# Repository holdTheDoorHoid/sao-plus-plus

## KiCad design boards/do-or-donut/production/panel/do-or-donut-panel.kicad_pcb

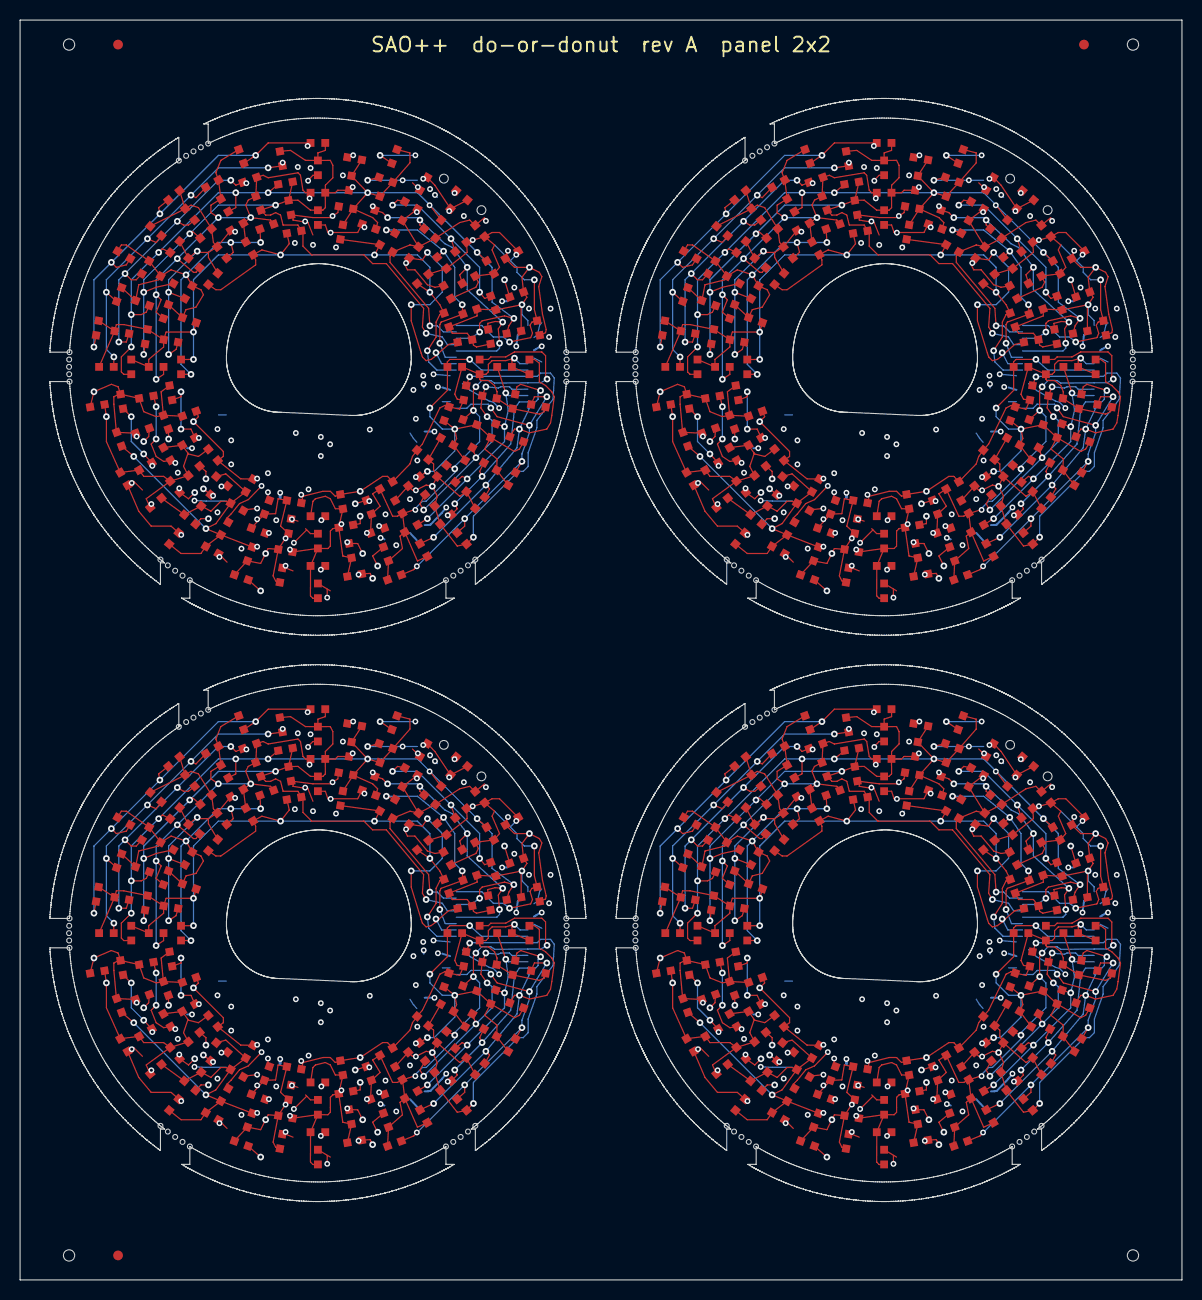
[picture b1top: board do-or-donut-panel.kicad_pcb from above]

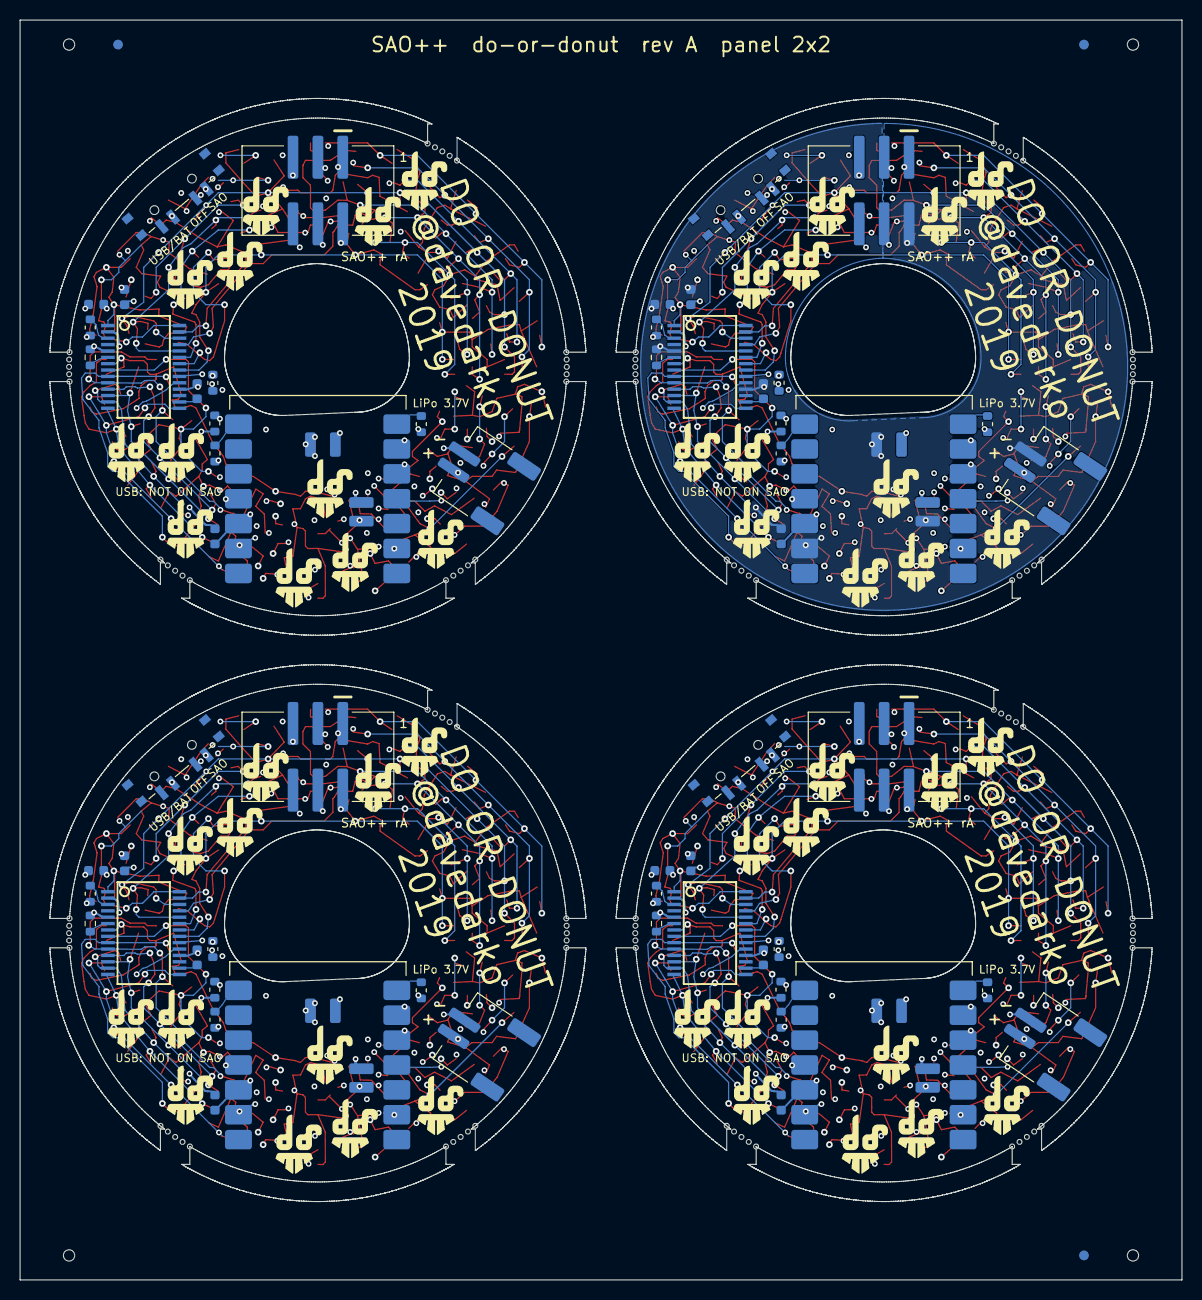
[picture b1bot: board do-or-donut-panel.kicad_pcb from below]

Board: 4 copper layers, 118.6 x 128.6 mm, 636 parts (60 on the bottom side), 136 nets.

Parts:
C101, C103, C104, C105, C201, C203, C204, C205, C301, C303, C304, C305, C401, C403, C404, C405: 100n; SAOPP_C_0603_1608Metric
DA101, DA102, DA103, DA104, DA105, DA106, DA107, DA108, DA109, DA110, DA111, DA112, DA113, DA114, DA115, DA116, DA117, DA118, DA119, DA120, DA121, DA122, DA123, DA124, DA125, DA126, DA127, DA128, DA129, DA130, DA131, DA132, DA133, DA134, DA135, DA136, DA137, DA138, DA139, DA140, DA141, DA142, DA143, DA144, DA145, DA146, DA147, DA148, DA149, DA150, DA151, DA152, DA153, DA154, DA155, DA156, DA157, DA158, DA159, DA160, DA161, DA162, DA163, DA164, DA165, DA166, DA167, DA168, DA169, DA170, DA171, DA172, DA201, DA202, DA203, DA204, DA205, DA206, DA207, DA208, DA209, DA210, DA211, DA212, DA213, DA214, DA215, DA216, DA217, DA218, DA219, DA220, DA221, DA222, DA223, DA224, DA225, DA226, DA227, DA228, DA229, DA230, DA231, DA232, DA233, DA234, DA235, DA236, DA237, DA238, DA239, DA240, DA241, DA242, DA243, DA244, DA245, DA246, DA247, DA248, DA249, DA250, DA251, DA252, DA253, DA254, DA255, DA256, DA257, DA258, DA259, DA260, DA261, DA262, DA263, DA264, DA265, DA266, DA267, DA268, DA269, DA270, DA271, DA272, DA301, DA302, DA303, DA304, DA305, DA306, DA307, DA308, DA309, DA310, DA311, DA312, DA313, DA314, DA315, DA316, DA317, DA318, DA319, DA320, DA321, DA322, DA323, DA324, DA325, DA326, DA327, DA328, DA329, DA330, DA331, DA332, DA333, DA334, DA335, DA336, DA337, DA338, DA339, DA340, DA341, DA342, DA343, DA344, DA345, DA346, DA347, DA348, DA349, DA350, DA351, DA352, DA353, DA354, DA355, DA356, DA357, DA358, DA359, DA360, DA361, DA362, DA363, DA364, DA365, DA366, DA367, DA368, DA369, DA370, DA371, DA372, DA401, DA402, DA403, DA404, DA405, DA406, DA407, DA408, DA409, DA410, DA411, DA412, DA413, DA414, DA415, DA416, DA417, DA418, DA419, DA420, DA421, DA422, DA423, DA424, DA425, DA426, DA427, DA428, DA429, DA430, DA431, DA432, DA433, DA434, DA435, DA436, DA437, DA438, DA439, DA440, DA441, DA442, DA443, DA444, DA445, DA446, DA447, DA448, DA449, DA450, DA451, DA452, DA453, DA454, DA455, DA456, DA457, DA458, DA459, DA460, DA461, DA462, DA463, DA464, DA465, DA466, DA467, DA468, DA469, DA470, DA471, DA472: LED 0603; LED_0603_CHIP-LED0603_davedarko
DB101, DB102, DB103, DB104, DB105, DB106, DB107, DB108, DB109, DB110, DB111, DB112, DB113, DB114, DB115, DB116, DB117, DB118, DB119, DB120, DB121, DB122, DB123, DB124, DB125, DB126, DB127, DB128, DB129, DB130, DB131, DB132, DB133, DB134, DB135, DB136, DB137, DB138, DB139, DB140, DB141, DB142, DB143, DB144, DB145, DB146, DB147, DB148, DB149, DB150, DB151, DB152, DB153, DB154, DB155, DB156, DB157, DB158, DB159, DB160, DB161, DB162, DB163, DB164, DB165, DB166, DB167, DB168, DB169, DB170, DB171, DB172, DB201, DB202, DB203, DB204, DB205, DB206, DB207, DB208, DB209, DB210, DB211, DB212, DB213, DB214, DB215, DB216, DB217, DB218, DB219, DB220, DB221, DB222, DB223, DB224, DB225, DB226, DB227, DB228, DB229, DB230, DB231, DB232, DB233, DB234, DB235, DB236, DB237, DB238, DB239, DB240, DB241, DB242, DB243, DB244, DB245, DB246, DB247, DB248, DB249, DB250, DB251, DB252, DB253, DB254, DB255, DB256, DB257, DB258, DB259, DB260, DB261, DB262, DB263, DB264, DB265, DB266, DB267, DB268, DB269, DB270, DB271, DB272, DB301, DB302, DB303, DB304, DB305, DB306, DB307, DB308, DB309, DB310, DB311, DB312, DB313, DB314, DB315, DB316, DB317, DB318, DB319, DB320, DB321, DB322, DB323, DB324, DB325, DB326, DB327, DB328, DB329, DB330, DB331, DB332, DB333, DB334, DB335, DB336, DB337, DB338, DB339, DB340, DB341, DB342, DB343, DB344, DB345, DB346, DB347, DB348, DB349, DB350, DB351, DB352, DB353, DB354, DB355, DB356, DB357, DB358, DB359, DB360, DB361, DB362, DB363, DB364, DB365, DB366, DB367, DB368, DB369, DB370, DB371, DB372, DB401, DB402, DB403, DB404, DB405, DB406, DB407, DB408, DB409, DB410, DB411, DB412, DB413, DB414, DB415, DB416, DB417, DB418, DB419, DB420, DB421, DB422, DB423, DB424, DB425, DB426, DB427, DB428, DB429, DB430, DB431, DB432, DB433, DB434, DB435, DB436, DB437, DB438, DB439, DB440, DB441, DB442, DB443, DB444, DB445, DB446, DB447, DB448, DB449, DB450, DB451, DB452, DB453, DB454, DB455, DB456, DB457, DB458, DB459, DB460, DB461, DB462, DB463, DB464, DB465, DB466, DB467, DB468, DB469, DB470, DB471, DB472: LED 0603; LED_0603_CHIP-LED0603_davedarko
J101, J201, J301, J401: SAO v1.69bis; SAOPP_CONN-01_BoxHeader_2x03_P2.54mm_SMD_XFCN_BH254VS-6P
J102, J202, J302, J402: LiPo 3.7 V; SAOPP_CONN-10_JST_PH_S2B-PH-SM4-TB_1x02_Horizontal
R101, R104, R105, R201, R204, R205, R301, R304, R305, R401, R404, R405: 1.3k; SAOPP_R_0603_1608Metric
R106, R206, R306, R406: 20k; R_0603_1608Metric
R107, R108, R207, R208, R307, R308, R407, R408: 330; SAOPP_R_0603_1608Metric
SW101, SW201, SW301, SW401: SAO / OFF / USB-BAT; SAOPP_SW-01_Slide_SP3T_CK_PCM13SMTR
U101, U201, U301, U401: IS31FL3731; SSOP-28_IS31FL3731_davedarko
U102, U202, U302, U402: XIAO ESP32-C3 / S3 / C6; SAOPP_MCU-01_Seeed_XIAO_SMD_C3_S3_C6

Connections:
B2-BAT+: J202.1, U202.15
B2-CA1: DA201.1, DA202.1, DA203.1, DA204.1, DA205.1, DA206.1, DA207.1, DA208.1, DA216.2, DA224.2, DA232.2, DA240.2, DA248.2, DA256.2, DA264.2, DA272.2, U201.21
B2-CA2: DA208.2, DA209.1, DA210.1, DA211.1, DA212.1, DA213.1, DA214.1, DA215.1, DA216.1, DA223.2, DA231.2, DA239.2, DA247.2, DA255.2, DA263.2, DA271.2, U201.22
B2-CA3: DA207.2, DA215.2, DA217.1, DA218.1, DA219.1, DA220.1, DA221.1, DA222.1, DA223.1, DA224.1, DA230.2, DA238.2, DA246.2, DA254.2, DA262.2, DA270.2, U201.23
B2-CA4: DA206.2, DA214.2, DA222.2, DA225.1, DA226.1, DA227.1, DA228.1, DA229.1, DA230.1, DA231.1, DA232.1, DA237.2, DA245.2, DA253.2, DA261.2, DA269.2, U201.24
B2-CA5: DA205.2, DA213.2, DA221.2, DA229.2, DA233.1, DA234.1, DA235.1, DA236.1, DA237.1, DA238.1, DA239.1, DA240.1, DA244.2, DA252.2, DA260.2, DA268.2, U201.25
B2-CA6: DA204.2, DA212.2, DA220.2, DA228.2, DA236.2, DA241.1, DA242.1, DA243.1, DA244.1, DA245.1, DA246.1, DA247.1, DA248.1, DA251.2, DA259.2, DA267.2, U201.26
B2-CA7: DA203.2, DA211.2, DA219.2, DA227.2, DA235.2, DA243.2, DA249.1, DA250.1, DA251.1, DA252.1, DA253.1, DA254.1, DA255.1, DA256.1, DA258.2, DA266.2, U201.27
B2-CA8: DA202.2, DA210.2, DA218.2, DA226.2, DA234.2, DA242.2, DA250.2, DA257.1, DA258.1, DA259.1, DA260.1, DA261.1, DA262.1, DA263.1, DA264.1, DA265.2, U201.28
B2-CA9: DA201.2, DA209.2, DA217.2, DA225.2, DA233.2, DA241.2, DA249.2, DA257.2, DA265.1, DA266.1, DA267.1, DA268.1, DA269.1, DA270.1, DA271.1, DA272.1, U201.1
B2-CB1: DB201.1, DB202.1, DB203.1, DB204.1, DB205.1, DB206.1, DB207.1, DB208.1, DB216.2, DB224.2, DB232.2, DB240.2, DB248.2, DB256.2, DB264.2, DB272.2, U201.7
B2-CB2: DB208.2, DB209.1, DB210.1, DB211.1, DB212.1, DB213.1, DB214.1, DB215.1, DB216.1, DB223.2, DB231.2, DB239.2, DB247.2, DB255.2, DB263.2, DB271.2, U201.8
B2-CB3: DB207.2, DB215.2, DB217.1, DB218.1, DB219.1, DB220.1, DB221.1, DB222.1, DB223.1, DB224.1, DB230.2, DB238.2, DB246.2, DB254.2, DB262.2, DB270.2, U201.9
B2-CB4: DB206.2, DB214.2, DB222.2, DB225.1, DB226.1, DB227.1, DB228.1, DB229.1, DB230.1, DB231.1, DB232.1, DB237.2, DB245.2, DB253.2, DB261.2, DB269.2, U201.10
B2-CB5: DB205.2, DB213.2, DB221.2, DB229.2, DB233.1, DB234.1, DB235.1, DB236.1, DB237.1, DB238.1, DB239.1, DB240.1, DB244.2, DB252.2, DB260.2, DB268.2, U201.11
B2-CB6: DB204.2, DB212.2, DB220.2, DB228.2, DB236.2, DB241.1, DB242.1, DB243.1, DB244.1, DB245.1, DB246.1, DB247.1, DB248.1, DB251.2, DB259.2, DB267.2, U201.12
B2-CB7: DB203.2, DB211.2, DB219.2, DB227.2, DB235.2, DB243.2, DB249.1, DB250.1, DB251.1, DB252.1, DB253.1, DB254.1, DB255.1, DB256.1, DB258.2, DB266.2, U201.13
B2-CB8: DB202.2, DB210.2, DB218.2, DB226.2, DB234.2, DB242.2, DB250.2, DB257.1, DB258.1, DB259.1, DB260.1, DB261.1, DB262.1, DB263.1, DB264.1, DB265.2, U201.14
B2-CB9: DB201.2, DB209.2, DB217.2, DB225.2, DB233.2, DB241.2, DB249.2, DB257.2, DB265.1, DB266.1, DB267.1, DB268.1, DB269.1, DB270.1, DB271.1, DB272.1, U201.15
B2-C_FILT: C201.1, U201.16
B2-D6_TX: R208.2, U202.7
B2-D7_RX: R207.2, U202.8
B2-GND: C201.2, C203.2, C204.2, C205.2, J201.2, J202.2, R206.2, U201.5, U201.18, U202.13, U202.16
B2-LED_SCL: R204.2, U201.20, U202.4
B2-LED_SDA: R205.2, U201.19, U202.11
B2-OFF_SENSE: SW201.2, U202.2
B2-R_EXT: R206.1, U201.6
B2-SAO_GPIO1: J201.5, R207.1
B2-SAO_GPIO2: J201.6, R208.1
B2-SCL: J201.4, U202.6
B2-SDA: J201.3, U202.5
B2-SDB: R201.2, U201.3
B2-V3V3: C203.1, C204.1, C205.1, R201.1, R204.1, R205.1, SW201.3, U201.2, U202.12
B2-VSAO: J201.1, SW201.1
B3-BAT+: J302.1, U302.15
B3-CA1: DA301.1, DA302.1, DA303.1, DA304.1, DA305.1, DA306.1, DA307.1, DA308.1, DA316.2, DA324.2, DA332.2, DA340.2, DA348.2, DA356.2, DA364.2, DA372.2, U301.21
B3-CA2: DA308.2, DA309.1, DA310.1, DA311.1, DA312.1, DA313.1, DA314.1, DA315.1, DA316.1, DA323.2, DA331.2, DA339.2, DA347.2, DA355.2, DA363.2, DA371.2, U301.22
B3-CA3: DA307.2, DA315.2, DA317.1, DA318.1, DA319.1, DA320.1, DA321.1, DA322.1, DA323.1, DA324.1, DA330.2, DA338.2, DA346.2, DA354.2, DA362.2, DA370.2, U301.23
B3-CA4: DA306.2, DA314.2, DA322.2, DA325.1, DA326.1, DA327.1, DA328.1, DA329.1, DA330.1, DA331.1, DA332.1, DA337.2, DA345.2, DA353.2, DA361.2, DA369.2, U301.24
B3-CA5: DA305.2, DA313.2, DA321.2, DA329.2, DA333.1, DA334.1, DA335.1, DA336.1, DA337.1, DA338.1, DA339.1, DA340.1, DA344.2, DA352.2, DA360.2, DA368.2, U301.25
B3-CA6: DA304.2, DA312.2, DA320.2, DA328.2, DA336.2, DA341.1, DA342.1, DA343.1, DA344.1, DA345.1, DA346.1, DA347.1, DA348.1, DA351.2, DA359.2, DA367.2, U301.26
B3-CA7: DA303.2, DA311.2, DA319.2, DA327.2, DA335.2, DA343.2, DA349.1, DA350.1, DA351.1, DA352.1, DA353.1, DA354.1, DA355.1, DA356.1, DA358.2, DA366.2, U301.27
B3-CA8: DA302.2, DA310.2, DA318.2, DA326.2, DA334.2, DA342.2, DA350.2, DA357.1, DA358.1, DA359.1, DA360.1, DA361.1, DA362.1, DA363.1, DA364.1, DA365.2, U301.28
B3-CA9: DA301.2, DA309.2, DA317.2, DA325.2, DA333.2, DA341.2, DA349.2, DA357.2, DA365.1, DA366.1, DA367.1, DA368.1, DA369.1, DA370.1, DA371.1, DA372.1, U301.1
B3-CB1: DB301.1, DB302.1, DB303.1, DB304.1, DB305.1, DB306.1, DB307.1, DB308.1, DB316.2, DB324.2, DB332.2, DB340.2, DB348.2, DB356.2, DB364.2, DB372.2, U301.7
B3-CB2: DB308.2, DB309.1, DB310.1, DB311.1, DB312.1, DB313.1, DB314.1, DB315.1, DB316.1, DB323.2, DB331.2, DB339.2, DB347.2, DB355.2, DB363.2, DB371.2, U301.8
B3-CB3: DB307.2, DB315.2, DB317.1, DB318.1, DB319.1, DB320.1, DB321.1, DB322.1, DB323.1, DB324.1, DB330.2, DB338.2, DB346.2, DB354.2, DB362.2, DB370.2, U301.9
B3-CB4: DB306.2, DB314.2, DB322.2, DB325.1, DB326.1, DB327.1, DB328.1, DB329.1, DB330.1, DB331.1, DB332.1, DB337.2, DB345.2, DB353.2, DB361.2, DB369.2, U301.10
B3-CB5: DB305.2, DB313.2, DB321.2, DB329.2, DB333.1, DB334.1, DB335.1, DB336.1, DB337.1, DB338.1, DB339.1, DB340.1, DB344.2, DB352.2, DB360.2, DB368.2, U301.11
B3-CB6: DB304.2, DB312.2, DB320.2, DB328.2, DB336.2, DB341.1, DB342.1, DB343.1, DB344.1, DB345.1, DB346.1, DB347.1, DB348.1, DB351.2, DB359.2, DB367.2, U301.12
B3-CB7: DB303.2, DB311.2, DB319.2, DB327.2, DB335.2, DB343.2, DB349.1, DB350.1, DB351.1, DB352.1, DB353.1, DB354.1, DB355.1, DB356.1, DB358.2, DB366.2, U301.13
B3-CB8: DB302.2, DB310.2, DB318.2, DB326.2, DB334.2, DB342.2, DB350.2, DB357.1, DB358.1, DB359.1, DB360.1, DB361.1, DB362.1, DB363.1, DB364.1, DB365.2, U301.14
B3-CB9: DB301.2, DB309.2, DB317.2, DB325.2, DB333.2, DB341.2, DB349.2, DB357.2, DB365.1, DB366.1, DB367.1, DB368.1, DB369.1, DB370.1, DB371.1, DB372.1, U301.15
B3-C_FILT: C301.1, U301.16
B3-D6_TX: R308.2, U302.7
B3-D7_RX: R307.2, U302.8
B3-GND: C301.2, C303.2, C304.2, C305.2, J301.2, J302.2, R306.2, U301.5, U301.18, U302.13, U302.16
B3-LED_SCL: R304.2, U301.20, U302.4
B3-LED_SDA: R305.2, U301.19, U302.11
B3-OFF_SENSE: SW301.2, U302.2
B3-R_EXT: R306.1, U301.6
B3-SAO_GPIO1: J301.5, R307.1
B3-SAO_GPIO2: J301.6, R308.1
B3-SCL: J301.4, U302.6
B3-SDA: J301.3, U302.5
B3-SDB: R301.2, U301.3
B3-V3V3: C303.1, C304.1, C305.1, R301.1, R304.1, R305.1, SW301.3, U301.2, U302.12
B3-VSAO: J301.1, SW301.1
B4-BAT+: J402.1, U402.15
B4-CA1: DA401.1, DA402.1, DA403.1, DA404.1, DA405.1, DA406.1, DA407.1, DA408.1, DA416.2, DA424.2, DA432.2, DA440.2, DA448.2, DA456.2, DA464.2, DA472.2, U401.21
B4-CA2: DA408.2, DA409.1, DA410.1, DA411.1, DA412.1, DA413.1, DA414.1, DA415.1, DA416.1, DA423.2, DA431.2, DA439.2, DA447.2, DA455.2, DA463.2, DA471.2, U401.22
B4-CA3: DA407.2, DA415.2, DA417.1, DA418.1, DA419.1, DA420.1, DA421.1, DA422.1, DA423.1, DA424.1, DA430.2, DA438.2, DA446.2, DA454.2, DA462.2, DA470.2, U401.23
B4-CA4: DA406.2, DA414.2, DA422.2, DA425.1, DA426.1, DA427.1, DA428.1, DA429.1, DA430.1, DA431.1, DA432.1, DA437.2, DA445.2, DA453.2, DA461.2, DA469.2, U401.24
B4-CA5: DA405.2, DA413.2, DA421.2, DA429.2, DA433.1, DA434.1, DA435.1, DA436.1, DA437.1, DA438.1, DA439.1, DA440.1, DA444.2, DA452.2, DA460.2, DA468.2, U401.25
B4-CA6: DA404.2, DA412.2, DA420.2, DA428.2, DA436.2, DA441.1, DA442.1, DA443.1, DA444.1, DA445.1, DA446.1, DA447.1, DA448.1, DA451.2, DA459.2, DA467.2, U401.26
B4-CA7: DA403.2, DA411.2, DA419.2, DA427.2, DA435.2, DA443.2, DA449.1, DA450.1, DA451.1, DA452.1, DA453.1, DA454.1, DA455.1, DA456.1, DA458.2, DA466.2, U401.27
B4-CA8: DA402.2, DA410.2, DA418.2, DA426.2, DA434.2, DA442.2, DA450.2, DA457.1, DA458.1, DA459.1, DA460.1, DA461.1, DA462.1, DA463.1, DA464.1, DA465.2, U401.28
B4-CA9: DA401.2, DA409.2, DA417.2, DA425.2, DA433.2, DA441.2, DA449.2, DA457.2, DA465.1, DA466.1, DA467.1, DA468.1, DA469.1, DA470.1, DA471.1, DA472.1, U401.1
B4-CB1: DB401.1, DB402.1, DB403.1, DB404.1, DB405.1, DB406.1, DB407.1, DB408.1, DB416.2, DB424.2, DB432.2, DB440.2, DB448.2, DB456.2, DB464.2, DB472.2, U401.7
B4-CB2: DB408.2, DB409.1, DB410.1, DB411.1, DB412.1, DB413.1, DB414.1, DB415.1, DB416.1, DB423.2, DB431.2, DB439.2, DB447.2, DB455.2, DB463.2, DB471.2, U401.8
B4-CB3: DB407.2, DB415.2, DB417.1, DB418.1, DB419.1, DB420.1, DB421.1, DB422.1, DB423.1, DB424.1, DB430.2, DB438.2, DB446.2, DB454.2, DB462.2, DB470.2, U401.9
B4-CB4: DB406.2, DB414.2, DB422.2, DB425.1, DB426.1, DB427.1, DB428.1, DB429.1, DB430.1, DB431.1, DB432.1, DB437.2, DB445.2, DB453.2, DB461.2, DB469.2, U401.10
B4-CB5: DB405.2, DB413.2, DB421.2, DB429.2, DB433.1, DB434.1, DB435.1, DB436.1, DB437.1, DB438.1, DB439.1, DB440.1, DB444.2, DB452.2, DB460.2, DB468.2, U401.11
B4-CB6: DB404.2, DB412.2, DB420.2, DB428.2, DB436.2, DB441.1, DB442.1, DB443.1, DB444.1, DB445.1, DB446.1, DB447.1, DB448.1, DB451.2, DB459.2, DB467.2, U401.12
B4-CB7: DB403.2, DB411.2, DB419.2, DB427.2, DB435.2, DB443.2, DB449.1, DB450.1, DB451.1, DB452.1, DB453.1, DB454.1, DB455.1, DB456.1, DB458.2, DB466.2, U401.13
B4-CB8: DB402.2, DB410.2, DB418.2, DB426.2, DB434.2, DB442.2, DB450.2, DB457.1, DB458.1, DB459.1, DB460.1, DB461.1, DB462.1, DB463.1, DB464.1, DB465.2, U401.14
B4-CB9: DB401.2, DB409.2, DB417.2, DB425.2, DB433.2, DB441.2, DB449.2, DB457.2, DB465.1, DB466.1, DB467.1, DB468.1, DB469.1, DB470.1, DB471.1, DB472.1, U401.15
B4-C_FILT: C401.1, U401.16
B4-D6_TX: R408.2, U402.7
B4-D7_RX: R407.2, U402.8
B4-GND: C401.2, C403.2, C404.2, C405.2, J401.2, J402.2, R406.2, U401.5, U401.18, U402.13, U402.16
B4-LED_SCL: R404.2, U401.20, U402.4
B4-LED_SDA: R405.2, U401.19, U402.11
B4-OFF_SENSE: SW401.2, U402.2
B4-R_EXT: R406.1, U401.6
B4-SAO_GPIO1: J401.5, R407.1
B4-SAO_GPIO2: J401.6, R408.1
B4-SCL: J401.4, U402.6
B4-SDA: J401.3, U402.5
B4-SDB: R401.2, U401.3
B4-V3V3: C403.1, C404.1, C405.1, R401.1, R404.1, R405.1, SW401.3, U401.2, U402.12
B4-VSAO: J401.1, SW401.1
BAT+: J102.1, U102.15
CA1: DA101.1, DA102.1, DA103.1, DA104.1, DA105.1, DA106.1, DA107.1, DA108.1, DA116.2, DA124.2, DA132.2, DA140.2, DA148.2, DA156.2, DA164.2, DA172.2, U101.21
CA2: DA108.2, DA109.1, DA110.1, DA111.1, DA112.1, DA113.1, DA114.1, DA115.1, DA116.1, DA123.2, DA131.2, DA139.2, DA147.2, DA155.2, DA163.2, DA171.2, U101.22
CA3: DA107.2, DA115.2, DA117.1, DA118.1, DA119.1, DA120.1, DA121.1, DA122.1, DA123.1, DA124.1, DA130.2, DA138.2, DA146.2, DA154.2, DA162.2, DA170.2, U101.23
CA4: DA106.2, DA114.2, DA122.2, DA125.1, DA126.1, DA127.1, DA128.1, DA129.1, DA130.1, DA131.1, DA132.1, DA137.2, DA145.2, DA153.2, DA161.2, DA169.2, U101.24
CA5: DA105.2, DA113.2, DA121.2, DA129.2, DA133.1, DA134.1, DA135.1, DA136.1, DA137.1, DA138.1, DA139.1, DA140.1, DA144.2, DA152.2, DA160.2, DA168.2, U101.25
CA6: DA104.2, DA112.2, DA120.2, DA128.2, DA136.2, DA141.1, DA142.1, DA143.1, DA144.1, DA145.1, DA146.1, DA147.1, DA148.1, DA151.2, DA159.2, DA167.2, U101.26
CA7: DA103.2, DA111.2, DA119.2, DA127.2, DA135.2, DA143.2, DA149.1, DA150.1, DA151.1, DA152.1, DA153.1, DA154.1, DA155.1, DA156.1, DA158.2, DA166.2, U101.27
CA8: DA102.2, DA110.2, DA118.2, DA126.2, DA134.2, DA142.2, DA150.2, DA157.1, DA158.1, DA159.1, DA160.1, DA161.1, DA162.1, DA163.1, DA164.1, DA165.2, U101.28
CA9: DA101.2, DA109.2, DA117.2, DA125.2, DA133.2, DA141.2, DA149.2, DA157.2, DA165.1, DA166.1, DA167.1, DA168.1, DA169.1, DA170.1, DA171.1, DA172.1, U101.1
CB1: DB101.1, DB102.1, DB103.1, DB104.1, DB105.1, DB106.1, DB107.1, DB108.1, DB116.2, DB124.2, DB132.2, DB140.2, DB148.2, DB156.2, DB164.2, DB172.2, U101.7
CB2: DB108.2, DB109.1, DB110.1, DB111.1, DB112.1, DB113.1, DB114.1, DB115.1, DB116.1, DB123.2, DB131.2, DB139.2, DB147.2, DB155.2, DB163.2, DB171.2, U101.8
CB3: DB107.2, DB115.2, DB117.1, DB118.1, DB119.1, DB120.1, DB121.1, DB122.1, DB123.1, DB124.1, DB130.2, DB138.2, DB146.2, DB154.2, DB162.2, DB170.2, U101.9
CB4: DB106.2, DB114.2, DB122.2, DB125.1, DB126.1, DB127.1, DB128.1, DB129.1, DB130.1, DB131.1, DB132.1, DB137.2, DB145.2, DB153.2, DB161.2, DB169.2, U101.10
CB5: DB105.2, DB113.2, DB121.2, DB129.2, DB133.1, DB134.1, DB135.1, DB136.1, DB137.1, DB138.1, DB139.1, DB140.1, DB144.2, DB152.2, DB160.2, DB168.2, U101.11
CB6: DB104.2, DB112.2, DB120.2, DB128.2, DB136.2, DB141.1, DB142.1, DB143.1, DB144.1, DB145.1, DB146.1, DB147.1, DB148.1, DB151.2, DB159.2, DB167.2, U101.12
CB7: DB103.2, DB111.2, DB119.2, DB127.2, DB135.2, DB143.2, DB149.1, DB150.1, DB151.1, DB152.1, DB153.1, DB154.1, DB155.1, DB156.1, DB158.2, DB166.2, U101.13
CB8: DB102.2, DB110.2, DB118.2, DB126.2, DB134.2, DB142.2, DB150.2, DB157.1, DB158.1, DB159.1, DB160.1, DB161.1, DB162.1, DB163.1, DB164.1, DB165.2, U101.14
CB9: DB101.2, DB109.2, DB117.2, DB125.2, DB133.2, DB141.2, DB149.2, DB157.2, DB165.1, DB166.1, DB167.1, DB168.1, DB169.1, DB170.1, DB171.1, DB172.1, U101.15
C_FILT: C101.1, U101.16
D6_TX: R108.2, U102.7
D7_RX: R107.2, U102.8
GND: C101.2, C103.2, C104.2, C105.2, J101.2, J102.2, R106.2, U101.5, U101.18, U102.13, U102.16
LED_SCL: R104.2, U101.20, U102.4
LED_SDA: R105.2, U101.19, U102.11
OFF_SENSE: SW101.2, U102.2
R_EXT: R106.1, U101.6
SAO_GPIO1: J101.5, R107.1
SAO_GPIO2: J101.6, R108.1
SCL: J101.4, U102.6
SDA: J101.3, U102.5
SDB: R101.2, U101.3
V3V3: C103.1, C104.1, C105.1, R101.1, R104.1, R105.1, SW101.3, U101.2, U102.12
VSAO: J101.1, SW101.1

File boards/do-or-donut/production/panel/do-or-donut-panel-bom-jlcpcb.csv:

Comment,Designator,Footprint,LCSC Part #
100n,"C101,C103,C104,C105,C201,C203,C204,C205,C301,C303,C304,C305,C401,C403,C404,C405",SAOPP_C_0603_1608Metric,C14663
LED 0603,"DA101,DA102,DA103,DA104,DA105,DA106,DA107,DA108,DA109,DA110,DA111,DA112,DA113,DA114,DA115,DA116,DA117,DA118,DA119,DA120,DA121,DA122,DA123,DA124,DA125,DA126,DA127,DA128,DA129,DA130,DA131,DA132,DA133,DA134,DA135,DA136,DA137,DA138,DA139,DA140,DA141,DA142,DA143,DA144,DA145,DA146,DA147,DA148,DA149,DA150,DA151,DA152,DA153,DA154,DA155,DA156,DA157,DA158,DA159,DA160,DA161,DA162,DA163,DA164,DA165,DA166,DA167,DA168,DA169,DA170,DA171,DA172,DA201,DA202,DA203,DA204,DA205,DA206,DA207,DA208,DA209,DA210,DA211,DA212,DA213,DA214,DA215,DA216,DA217,DA218,DA219,DA220,DA221,DA222,DA223,DA224,DA225,DA226,DA227,DA228,DA229,DA230,DA231,DA232,DA233,DA234,DA235,DA236,DA237,DA238,DA239,DA240,DA241,DA242,DA243,DA244,DA245,DA246,DA247,DA248,DA249,DA250,DA251,DA252,DA253,DA254,DA255,DA256,DA257,DA258,DA259,DA260,DA261,DA262,DA263,DA264,DA265,DA266,DA267,DA268,DA269,DA270,DA271,DA272,DA301,DA302,DA303,DA304,DA305,DA306,DA307,DA308,DA309,DA310,DA311,DA312,DA313,DA314,DA315,DA316,DA317,DA318,DA319,DA320,DA321,DA322,DA323,DA324,DA325,DA326,DA327,DA328,DA329,DA330,DA331,DA332,DA333,DA334,DA335,DA336,DA337,DA338,DA339,DA340,DA341,DA342,DA343,DA344,DA345,DA346,DA347,DA348,DA349,DA350,DA351,DA352,DA353,DA354,DA355,DA356,DA357,DA358,DA359,DA360,DA361,DA362,DA363,DA364,DA365,DA366,DA367,DA368,DA369,DA370,DA371,DA372,DA401,DA402,DA403,DA404,DA405,DA406,DA407,DA408,DA409,DA410,DA411,DA412,DA413,DA414,DA415,DA416,DA417,DA418,DA419,DA420,DA421,DA422,DA423,DA424,DA425,DA426,DA427,DA428,DA429,DA430,DA431,DA432,DA433,DA434,DA435,DA436,DA437,DA438,DA439,DA440,DA441,DA442,DA443,DA444,DA445,DA446,DA447,DA448,DA449,DA450,DA451,DA452,DA453,DA454,DA455,DA456,DA457,DA458,DA459,DA460,DA461,DA462,DA463,DA464,DA465,DA466,DA467,DA468,DA469,DA470,DA471,DA472,DB101,DB102,DB103,DB104,DB105,DB106,DB107,DB108,DB109,DB110,DB111,DB112,DB113,DB114,DB115,DB116,DB117,DB118,DB119,DB120,DB121,DB122,DB123,DB124,DB125,DB126,DB127,DB128,DB129,DB130,DB131,DB132,DB133,DB134,DB135,DB136,DB137,DB138,DB139,DB140,DB141,DB142,DB143,DB144,DB145,DB146,DB147,DB148,DB149,DB150,DB151,DB152,DB153,DB154,DB155,DB156,DB157,DB158,DB159,DB160,DB161,DB162,DB163,DB164,DB165,DB166,DB167,DB168,DB169,DB170,DB171,DB172,DB201,DB202,DB203,DB204,DB205,DB206,DB207,DB208,DB209,DB210,DB211,DB212,DB213,DB214,DB215,DB216,DB217,DB218,DB219,DB220,DB221,DB222,DB223,DB224,DB225,DB226,DB227,DB228,DB229,DB230,DB231,DB232,DB233,DB234,DB235,DB236,DB237,DB238,DB239,DB240,DB241,DB242,DB243,DB244,DB245,DB246,DB247,DB248,DB249,DB250,DB251,DB252,DB253,DB254,DB255,DB256,DB257,DB258,DB259,DB260,DB261,DB262,DB263,DB264,DB265,DB266,DB267,DB268,DB269,DB270,DB271,DB272,DB301,DB302,DB303,DB304,DB305,DB306,DB307,DB308,DB309,DB310,DB311,DB312,DB313,DB314,DB315,DB316,DB317,DB318,DB319,DB320,DB321,DB322,DB323,DB324,DB325,DB326,DB327,DB328,DB329,DB330,DB331,DB332,DB333,DB334,DB335,DB336,DB337,DB338,DB339,DB340,DB341,DB342,DB343,DB344,DB345,DB346,DB347,DB348,DB349,DB350,DB351,DB352,DB353,DB354,DB355,DB356,DB357,DB358,DB359,DB360,DB361,DB362,DB363,DB364,DB365,DB366,DB367,DB368,DB369,DB370,DB371,DB372,DB401,DB402,DB403,DB404,DB405,DB406,DB407,DB408,DB409,DB410,DB411,DB412,DB413,DB414,DB415,DB416,DB417,DB418,DB419,DB420,DB421,DB422,DB423,DB424,DB425,DB426,DB427,DB428,DB429,DB430,DB431,DB432,DB433,DB434,DB435,DB436,DB437,DB438,DB439,DB440,DB441,DB442,DB443,DB444,DB445,DB446,DB447,DB448,DB449,DB450,DB451,DB452,DB453,DB454,DB455,DB456,DB457,DB458,DB459,DB460,DB461,DB462,DB463,DB464,DB465,DB466,DB467,DB468,DB469,DB470,DB471,DB472",LED_0603_CHIP-LED0603_davedarko,
SAO v1.69bis,"J101,J201,J301,J401",SAOPP_CONN-01_BoxHeader_2x03_P2.54mm_SMD_XFCN_BH254VS-6P,C492445
LiPo 3.7 V,"J102,J202,J302,J402",SAOPP_CONN-10_JST_PH_S2B-PH-SM4-TB_1x02_Horizontal,C295747
1.3k,"R101,R104,R105,R201,R204,R205,R301,R304,R305,R401,R404,R405",SAOPP_R_0603_1608Metric,C22767
20k,"R106,R206,R306,R406",R_0603_1608Metric,C4184
330,"R107,R108,R207,R208,R307,R308,R407,R408",SAOPP_R_0603_1608Metric,C23138
SAO / OFF / USB-BAT,"SW101,SW201,SW301,SW401",SAOPP_SW-01_Slide_SP3T_CK_PCM13SMTR,C221842
IS31FL3731,"U101,U201,U301,U401",SSOP-28_IS31FL3731_davedarko,C2940545
XIAO ESP32-C3 / S3 / C6,"U102,U202,U302,U402",SAOPP_MCU-01_Seeed_XIAO_SMD_C3_S3_C6,

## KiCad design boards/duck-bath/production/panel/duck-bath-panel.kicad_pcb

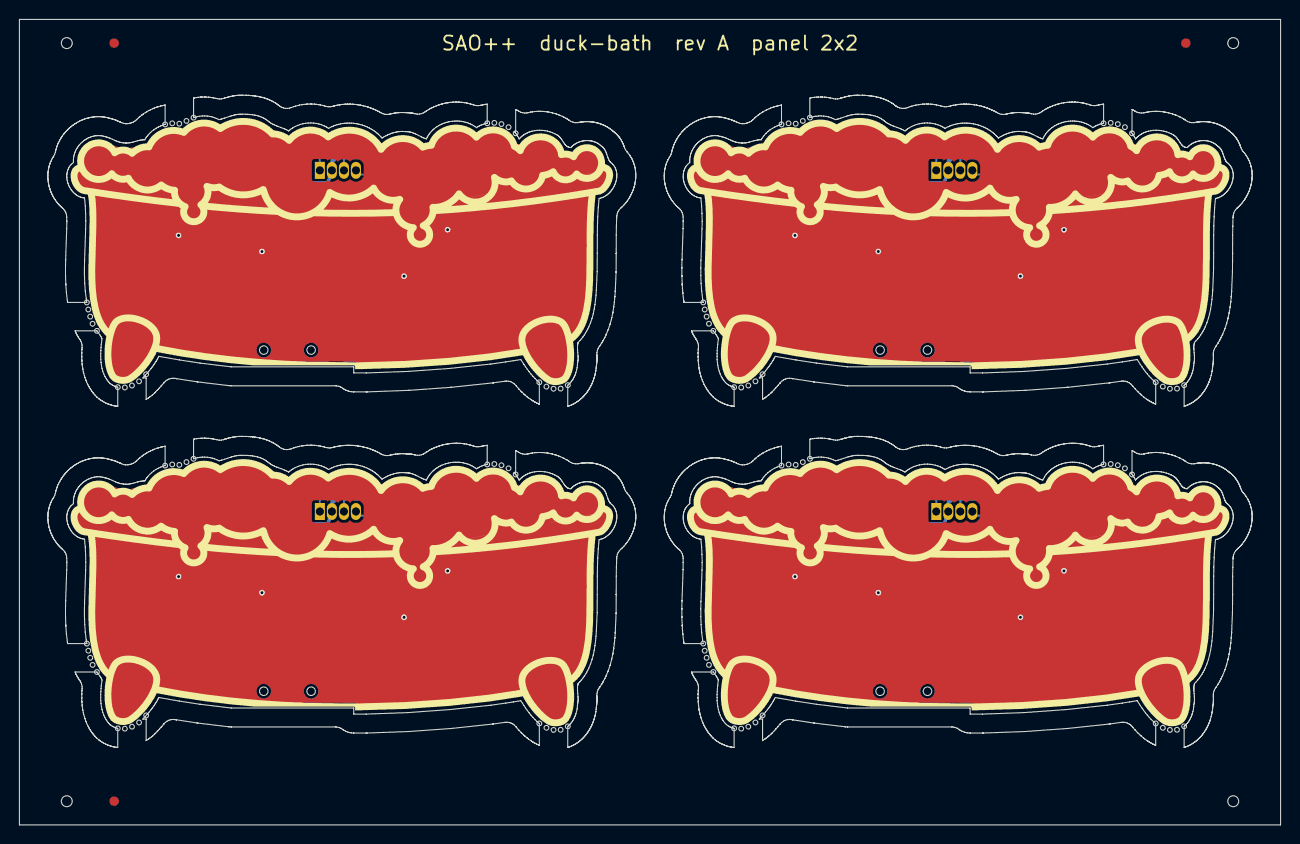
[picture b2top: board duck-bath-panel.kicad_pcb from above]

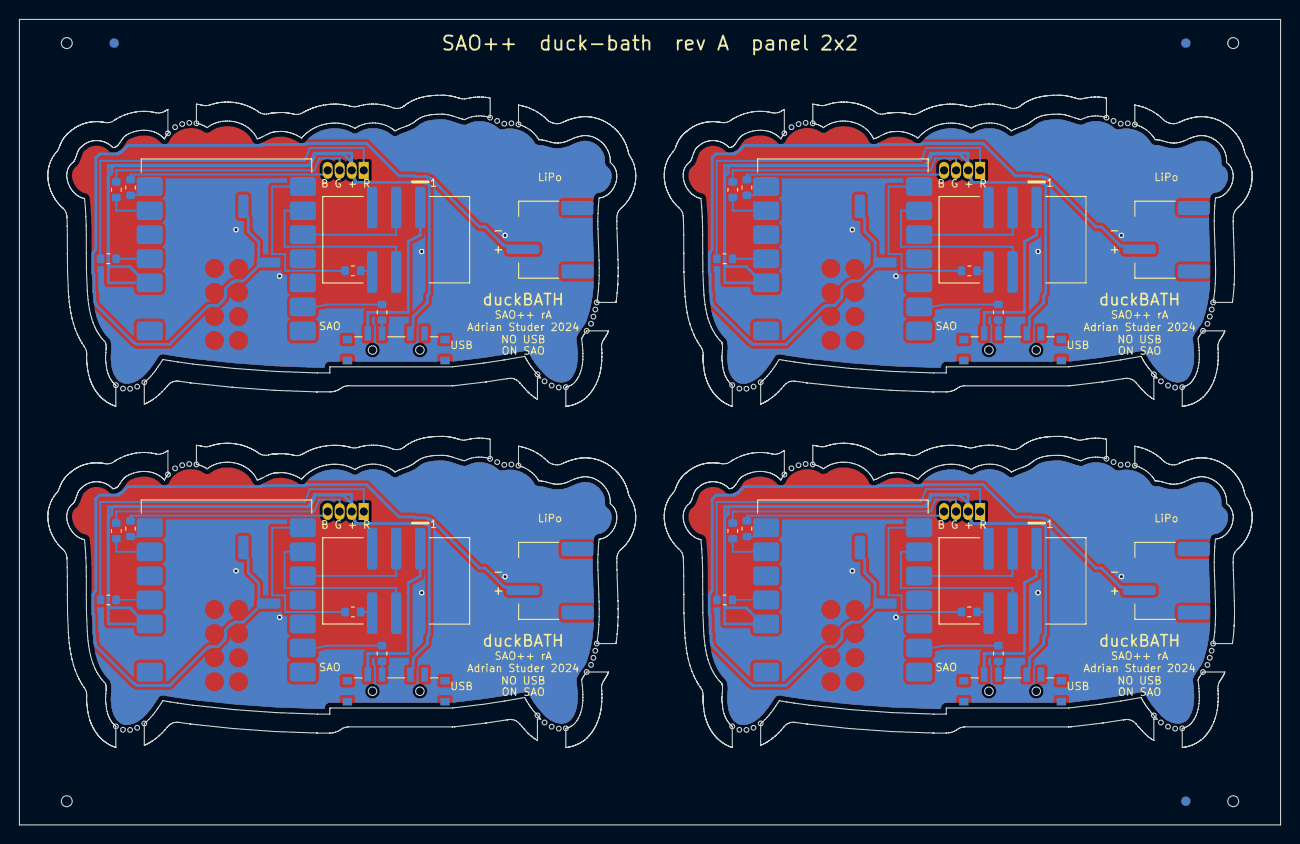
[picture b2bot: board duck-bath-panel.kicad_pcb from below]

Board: 2 copper layers, 133.1 x 85.0 mm, 40 parts (36 on the bottom side), 64 nets.

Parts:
D101, D201, D301, D401: RGB 5mm CA; LED_D5.0mm-4_RGB_single-side
J101, J201, J301, J401: SAO v1.69bis; SAOPP_CONN-01_BoxHeader_2x03_P2.54mm_SMD_XFCN_BH254VS-6P
J102, J202, J302, J402: LiPo 3.7 V; SAOPP_CONN-10_JST_PH_S2B-PH-SM4-TB_1x02_Horizontal
R101, R102, R103, R201, R202, R203, R301, R302, R303, R401, R402, R403: 100; R_0603_1608Metric
R104, R106, R204, R206, R304, R306, R404, R406: 330; SAOPP_R_0603_1608Metric
SW101, SW201, SW301, SW401: SAO / OFF / USB-BAT; SAOPP_SW-01_Slide_SP3T_CK_PCM13SMTR
U101, U201, U301, U401: XIAO ESP32-C3 / S3 / C6; SAOPP_MCU-01_Seeed_XIAO_SMD_C3_S3_C6

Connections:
B2-BAT+: J202.1, U201.15
B2-D6_TX: R206.2, U201.7
B2-GND: J201.2, J202.2, U201.13, U201.16
B2-LED_B: R203.1, U201.8
B2-LED_BK: D201.4, R203.2
B2-LED_G: R202.1, U201.9
B2-LED_GK: D201.3, R202.2
B2-LED_R: R201.1, U201.11
B2-LED_RK: D201.1, R201.2
B2-OFF_SENSE: R204.2, U201.2
B2-OFF_SW: R204.1, SW201.2
B2-SAO_GPIO2: J201.6, R206.1
B2-SCL: J201.4, U201.6
B2-SDA: J201.3, U201.5
B2-V3V3: D201.2, SW201.3, U201.12
B2-VSAO: J201.1, SW201.1
B3-BAT+: J302.1, U301.15
B3-D6_TX: R306.2, U301.7
B3-GND: J301.2, J302.2, U301.13, U301.16
B3-LED_B: R303.1, U301.8
B3-LED_BK: D301.4, R303.2
B3-LED_G: R302.1, U301.9
B3-LED_GK: D301.3, R302.2
B3-LED_R: R301.1, U301.11
B3-LED_RK: D301.1, R301.2
B3-OFF_SENSE: R304.2, U301.2
B3-OFF_SW: R304.1, SW301.2
B3-SAO_GPIO2: J301.6, R306.1
B3-SCL: J301.4, U301.6
B3-SDA: J301.3, U301.5
B3-V3V3: D301.2, SW301.3, U301.12
B3-VSAO: J301.1, SW301.1
B4-BAT+: J402.1, U401.15
B4-D6_TX: R406.2, U401.7
B4-GND: J401.2, J402.2, U401.13, U401.16
B4-LED_B: R403.1, U401.8
B4-LED_BK: D401.4, R403.2
B4-LED_G: R402.1, U401.9
B4-LED_GK: D401.3, R402.2
B4-LED_R: R401.1, U401.11
B4-LED_RK: D401.1, R401.2
B4-OFF_SENSE: R404.2, U401.2
B4-OFF_SW: R404.1, SW401.2
B4-SAO_GPIO2: J401.6, R406.1
B4-SCL: J401.4, U401.6
B4-SDA: J401.3, U401.5
B4-V3V3: D401.2, SW401.3, U401.12
B4-VSAO: J401.1, SW401.1
BAT+: J102.1, U101.15
D6_TX: R106.2, U101.7
GND: J101.2, J102.2, U101.13, U101.16
LED_B: R103.1, U101.8
LED_BK: D101.4, R103.2
LED_G: R102.1, U101.9
LED_GK: D101.3, R102.2
LED_R: R101.1, U101.11
LED_RK: D101.1, R101.2
OFF_SENSE: R104.2, U101.2
OFF_SW: R104.1, SW101.2
SAO_GPIO2: J101.6, R106.1
SCL: J101.4, U101.6
SDA: J101.3, U101.5
V3V3: D101.2, SW101.3, U101.12
VSAO: J101.1, SW101.1

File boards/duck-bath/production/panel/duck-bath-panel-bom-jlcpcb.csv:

Comment,Designator,Footprint,LCSC Part #
RGB 5mm CA,"D101,D201,D301,D401",LED_D5.0mm-4_RGB_single-side,
SAO v1.69bis,"J101,J201,J301,J401",SAOPP_CONN-01_BoxHeader_2x03_P2.54mm_SMD_XFCN_BH254VS-6P,C492445
LiPo 3.7 V,"J102,J202,J302,J402",SAOPP_CONN-10_JST_PH_S2B-PH-SM4-TB_1x02_Horizontal,C295747
100,"R101,R102,R103,R201,R202,R203,R301,R302,R303,R401,R402,R403",R_0603_1608Metric,C22775
330,"R104,R106,R204,R206,R304,R306,R404,R406",SAOPP_R_0603_1608Metric,C23138
SAO / OFF / USB-BAT,"SW101,SW201,SW301,SW401",SAOPP_SW-01_Slide_SP3T_CK_PCM13SMTR,C221842
XIAO ESP32-C3 / S3 / C6,"U101,U201,U301,U401",SAOPP_MCU-01_Seeed_XIAO_SMD_C3_S3_C6,

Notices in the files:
boards/duck-jaws/production/panel/duck-jaws-panel.kicad_pcb:
Original design: duckGLOW / duckJAWS v0.2, (c) 2024 Adrian Studer (astuder), CERN-OHL-P, github.com/astuder/duckglow
CERN-OHL-P  astuder/duckglow
boards/floppy-disk/hardware/floppy-disk.kicad_pcb:
© 2020 Uri Shaked
